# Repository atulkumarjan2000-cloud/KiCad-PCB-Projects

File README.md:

# KiCad-PCB-Projects
A collection of my KiCad Schematic, PCB design, Gerber and hardware projects

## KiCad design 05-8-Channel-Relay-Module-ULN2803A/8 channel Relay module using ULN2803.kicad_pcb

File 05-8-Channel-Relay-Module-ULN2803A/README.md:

# 8-Channel Relay Module Using ULN2803A

## Project Overview
This project focuses on designing an 8-channel relay module using KiCad EDA. The circuit uses a ULN2803A Darlington transistor array to drive eight relay channels from external control inputs.

## Features
- 8 independent relay output channels
- ULN2803A relay driver IC
- Input resistor network
- Individual LED indicators for relay channels
- Power input and status LED
- PCB design with mounting holes

## Design Tools
- KiCad EDA
- Schematic Design
- PCB Layout Design
- 3D PCB Visualization

## Project Files
- `8 Channel Relay Module using ULN2803.kicad_sch` — circuit schematic
- `8 Channel Relay Module using ULN2803.kicad_pcb` — PCB layout, when completed
- `8 Channel Relay Module using ULN2803.kicad_pro` — KiCad project configuration

## Applications
- Embedded systems
- Industrial control prototypes
- Home automation
- Microcontroller-based relay switching

## Safety Note
Verify relay coil voltage, contact ratings, driver connections, and PCB clearances before powering the circuit. Mains-voltage applications require appropriate isolation and safe enclosure design.

## Author
Atul

Designed using KiCad EDA.

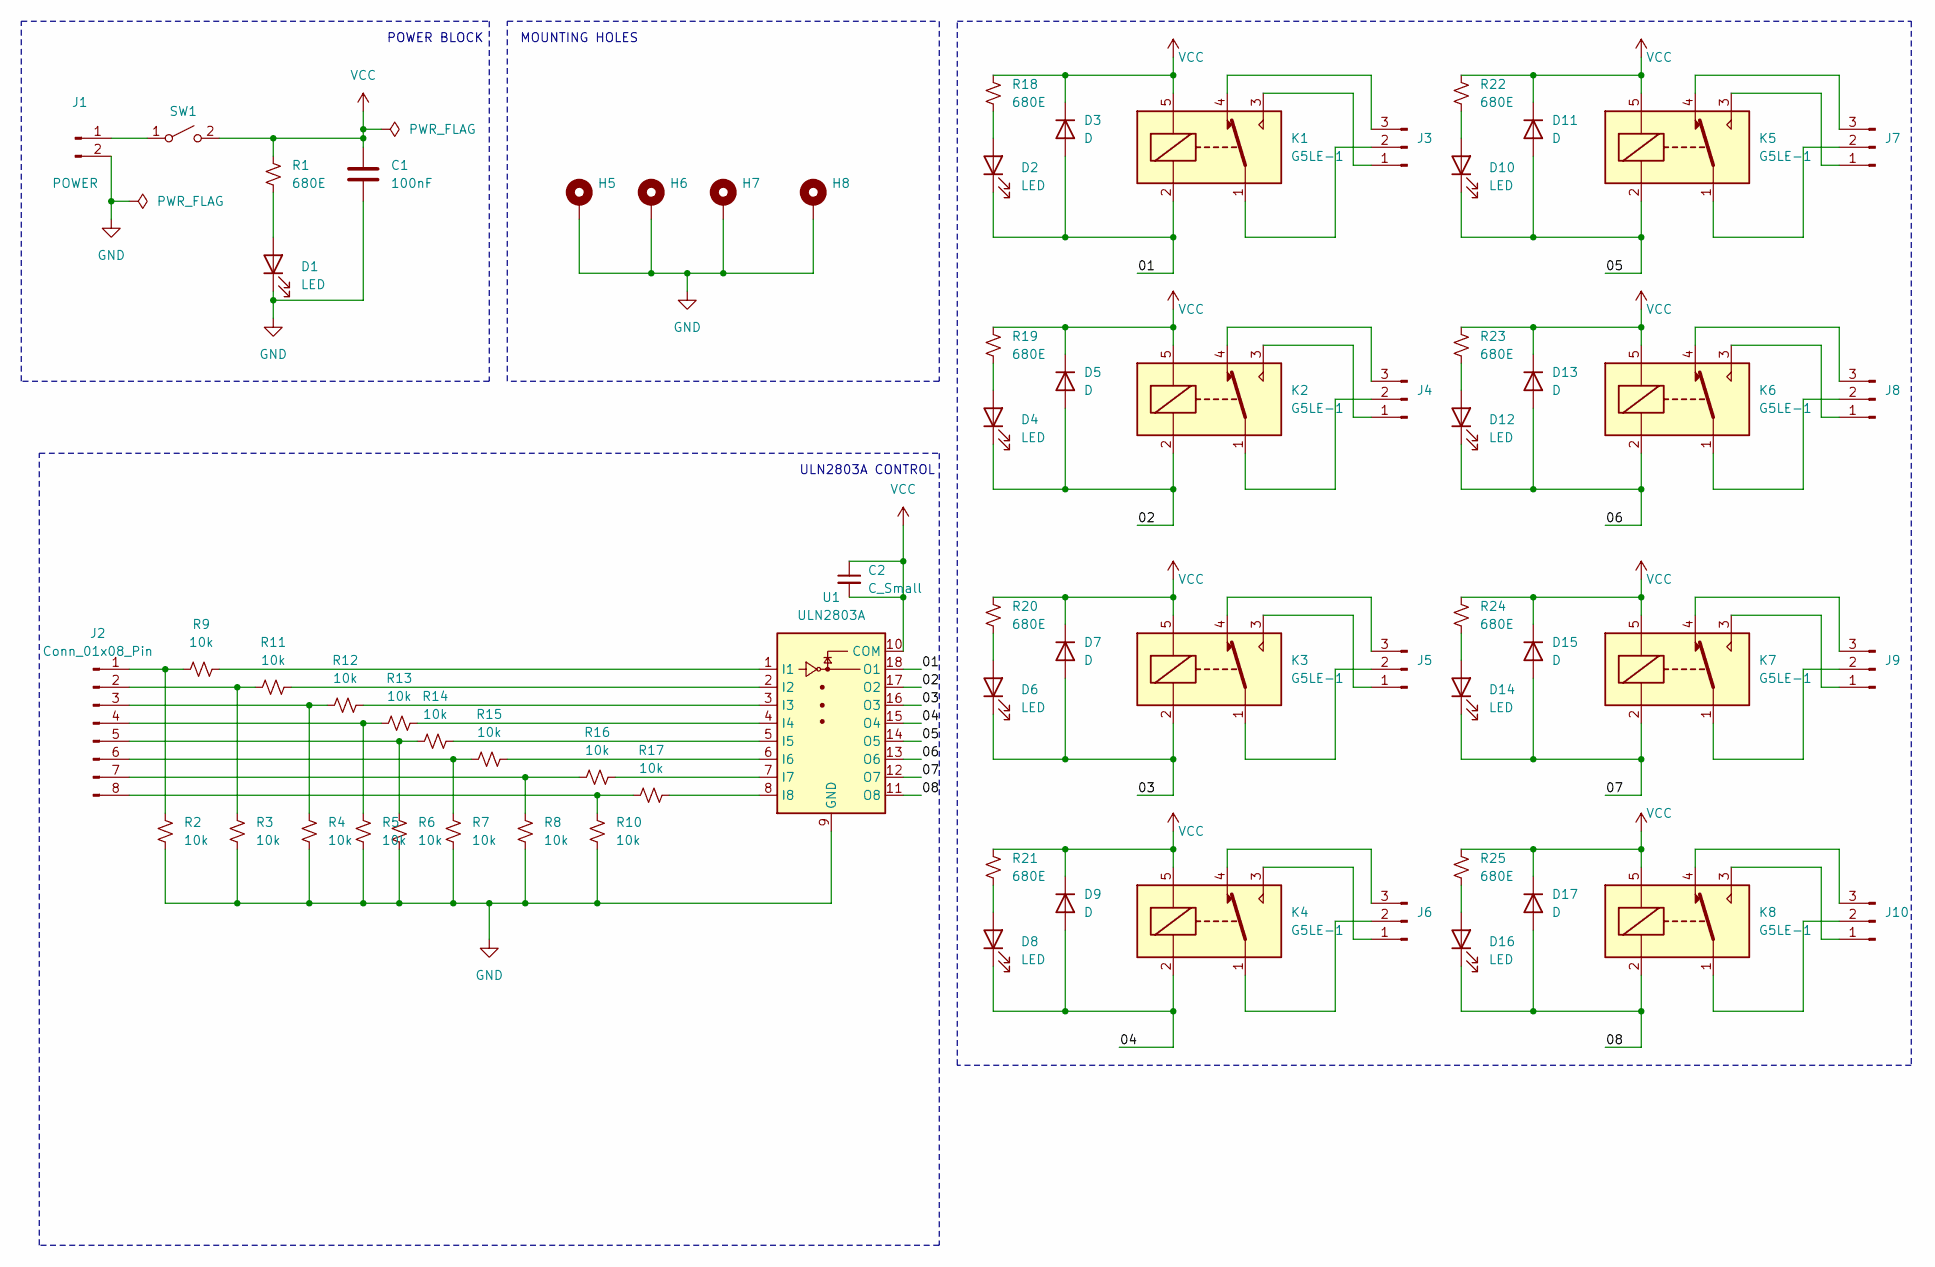
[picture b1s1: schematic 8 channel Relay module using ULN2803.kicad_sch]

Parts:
C1: 100nF; C_0805_2012Metric
C2: C_Small; C_0805_2012Metric
D1, D2, D4, D6, D8, D10, D12, D14, D16: LED; LED_1206_3216Metric
D3, D5, D7, D9, D11, D13, D15, D17: D; D_1206_3216Metric
H5, H6, H7, H8: MountingHole_Pad; MountingHole_2.5mm_Pad_Via
J1: POWER; JST_NV_B02P-NV_1x02_P5.00mm_Vertical
J2: Conn_01x08_Pin; PinHeader_1x08_P2.54mm_Vertical
J3, J4, J5, J6, J7, J8, J9, J10: Conn_01x03_Pin; JST_NV_B03P-NV_1x03_P5.00mm_Vertical
K1, K2, K3, K4, K5, K6, K7, K8: G5LE-1; Relay_SPDT_Omron-G5LE-1
R1, R18, R19, R20, R21, R22, R23, R24, R25: 680E; R_0805_2012Metric
R2, R3, R4, R5, R6, R7, R8, R9, R10, R11, R12, R13, R14, R15, R16, R17: 10k; R_0805_2012Metric
SW1: SW_DIP_SPSTx01_Slide_Copal_CHS-01A_W5.08mm_P1.27mm_JPin
U1: ULN2803A; DIP850W46P254L2324H393Q18

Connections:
/01: D2.1 (K), D3.2 (A), K1.2, U1.18 (O1)
/02: D4.1 (K), D5.2 (A), K2.2, U1.17 (O2)
/03: D6.1 (K), D7.2 (A), K3.2, U1.16 (O3)
/04: D8.1 (K), D9.2 (A), K4.2, U1.15 (O4)
/05: D10.1 (K), D11.2 (A), K5.2, U1.14 (O5)
/06: D12.1 (K), D13.2 (A), K6.2, U1.13 (O6)
/07: D14.1 (K), D15.2 (A), K7.2, U1.12 (O7)
/08: D16.1 (K), D17.2 (A), K8.2, U1.11 (O8)
GND: C1.2, D1.1 (K), H5.1 (1_1), H6.1 (1_1), H7.1 (1_1), H8.1 (1_1), J1.2, R2.2, R3.2, R4.2, R5.2, R6.2, R7.2, R8.2, R10.2, U1.9 (GND)
unnamed: D1.2 (A), R1.2
unnamed: D2.2 (A), R18.2
unnamed: D4.2 (A), R19.2
unnamed: D6.2 (A), R20.2
unnamed: D8.2 (A), R21.2
unnamed: D10.2 (A), R22.2
unnamed: D12.2 (A), R23.2
unnamed: D14.2 (A), R24.2
unnamed: D16.2 (A), R25.2
unnamed: J1.1, SW1.1 (A)
unnamed: J2.1, R2.1, R9.1
unnamed: J2.2, R3.1, R11.1
unnamed: J2.3, R4.1, R12.1
unnamed: J2.4, R5.1, R13.1
unnamed: J2.5, R6.1, R14.1
unnamed: J2.6, R7.1, R15.1
unnamed: J2.7, R8.1, R16.1
unnamed: J2.8, R10.1, R17.1
unnamed: J3.1, K1.3
unnamed: J3.2, K1.1
unnamed: J3.3, K1.4
unnamed: J4.1, K2.3
unnamed: J4.2, K2.1
unnamed: J4.3, K2.4
unnamed: J5.1, K3.3
unnamed: J5.2, K3.1
unnamed: J5.3, K3.4
unnamed: J6.1, K4.3
unnamed: J6.2, K4.1
unnamed: J6.3, K4.4
unnamed: J7.1, K5.3
unnamed: J7.2, K5.1
unnamed: J7.3, K5.4
unnamed: J8.1, K6.3
unnamed: J8.2, K6.1
unnamed: J8.3, K6.4
unnamed: J9.1, K7.3
unnamed: J9.2, K7.1
unnamed: J9.3, K7.4
unnamed: J10.1, K8.3
unnamed: J10.2, K8.1
unnamed: J10.3, K8.4
unnamed: R9.2, U1.1 (I1)
unnamed: R11.2, U1.2 (I2)
unnamed: R12.2, U1.3 (I3)
unnamed: R13.2, U1.4 (I4)
unnamed: R14.2, U1.5 (I5)
unnamed: R15.2, U1.6 (I6)
unnamed: R16.2, U1.7 (I7)
unnamed: R17.2, U1.8 (I8)
VCC: C1.1, C2.1, C2.2, D3.1 (K), D5.1 (K), D7.1 (K), D9.1 (K), D11.1 (K), D13.1 (K), D15.1 (K), D17.1 (K), K1.5, K2.5, K3.5, K4.5, K5.5, K6.5, K7.5, K8.5, R1.1, R18.1, R19.1, R20.1, R21.1, R22.1, R23.1, R24.1, R25.1, SW1.2 (B), U1.10 (COM)

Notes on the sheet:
MOUNTING HOLES
ULN2803A CONTROL
POWER BLOCK

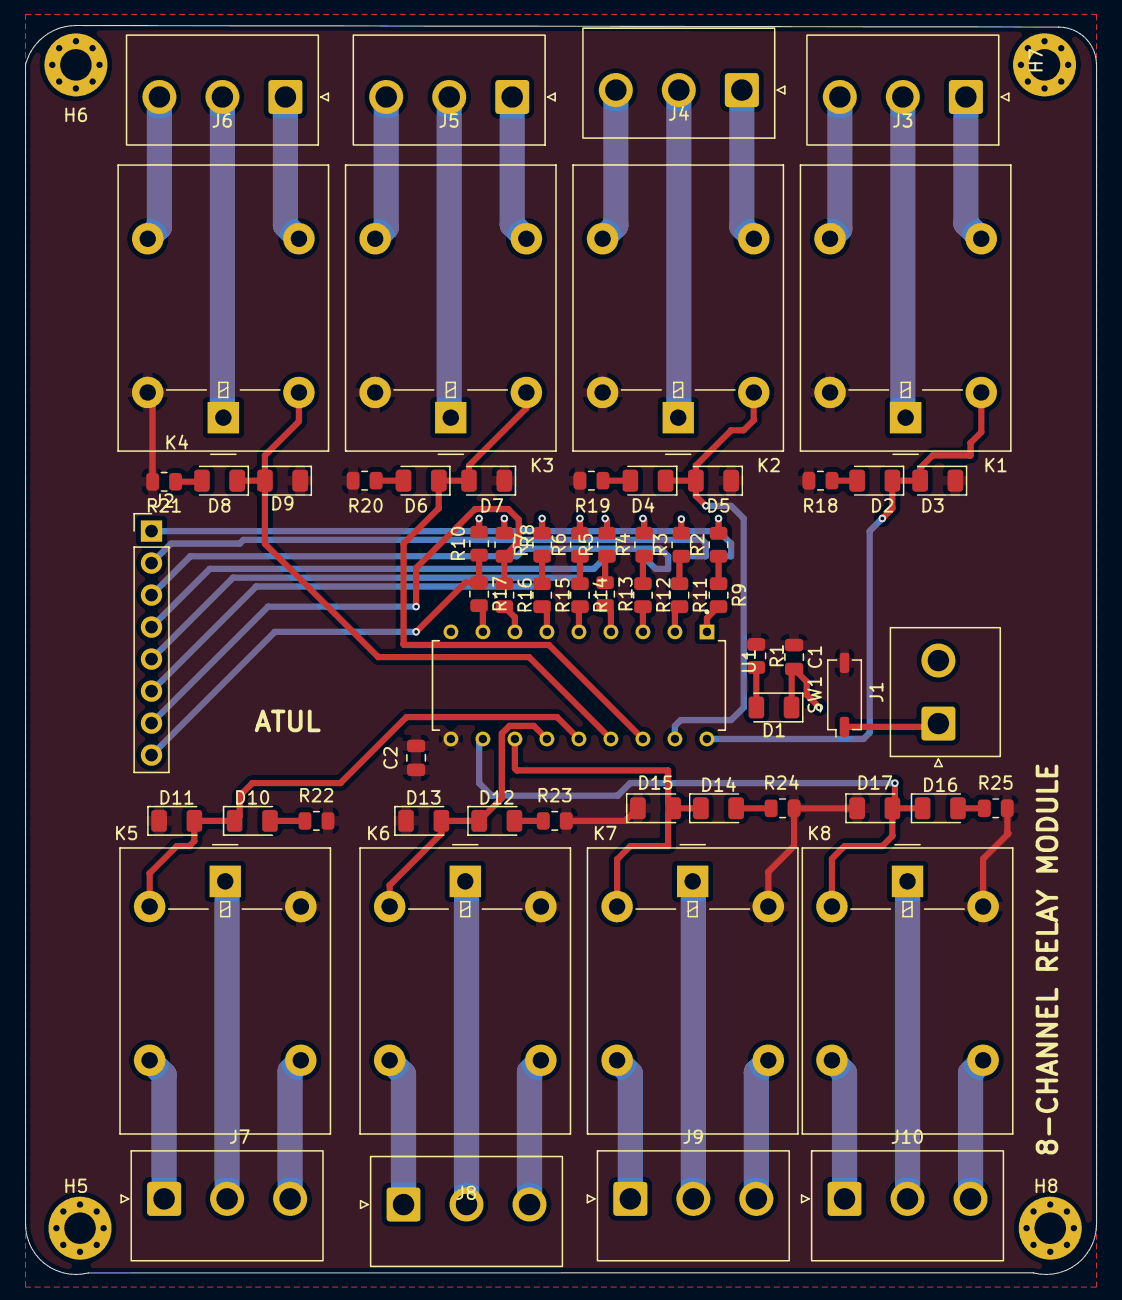
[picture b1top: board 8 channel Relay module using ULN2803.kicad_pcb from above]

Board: 2 copper layers, 85.0 x 99.1 mm, 68 parts (0 on the bottom side), 60 nets.

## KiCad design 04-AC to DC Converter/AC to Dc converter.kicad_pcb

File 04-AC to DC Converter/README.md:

# 12V AC to DC Converter

A custom 12V AC to DC  Converter/rectifier and filtered power supply PCB designed using KiCad.

## Project Overview

This project converts 12V AC input into filtered DC output using a full-wave bridge rectifier and smoothing capacitor.

## Main Components

- D1–D4: Bridge Rectifier
- C1: Smoothing Capacitor
- D5: Power Indicator LED
- R1/R2: Resistors
- J1: 12V AC Input
- J2: DC Output

## Tools Used

- KiCad
- Schematic Design
- PCB Design

## PCB Views

### 3D View

### PCB Layout

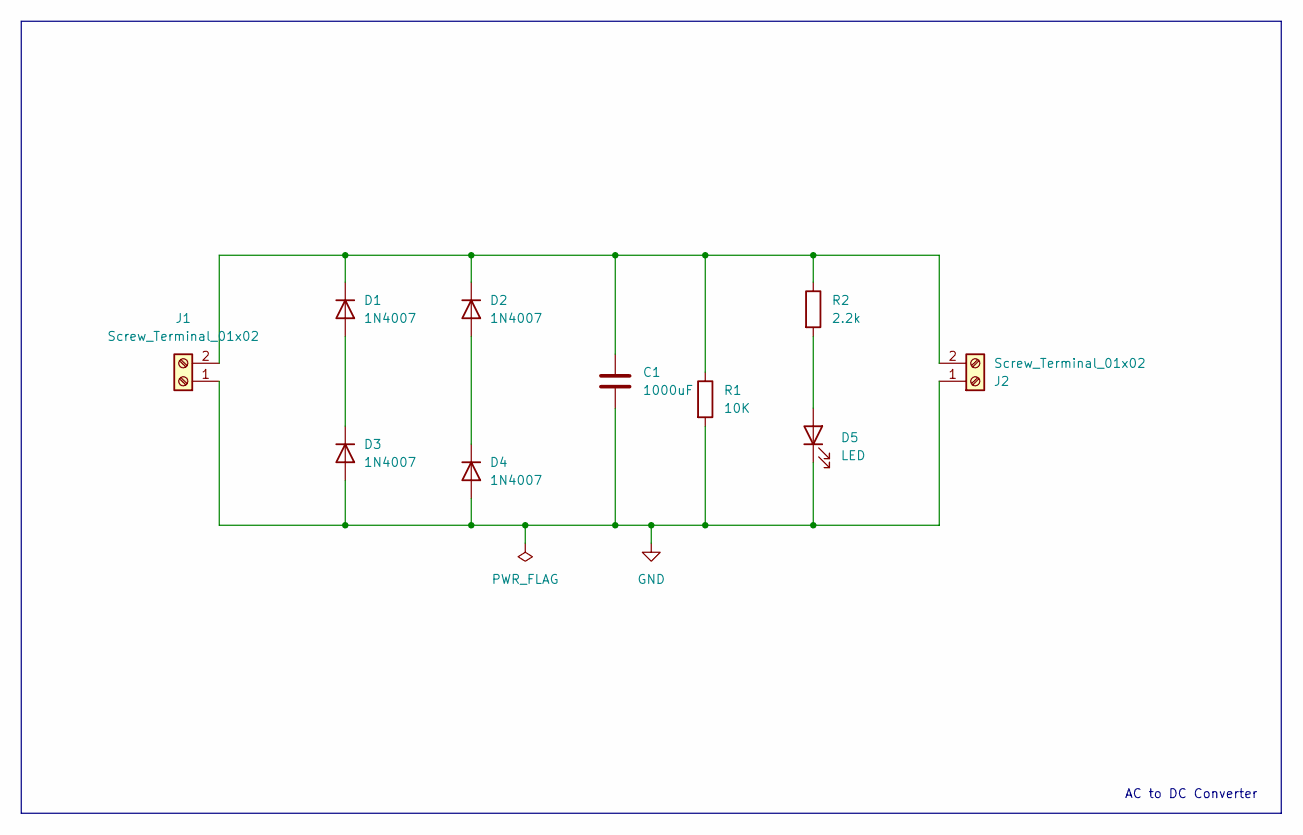
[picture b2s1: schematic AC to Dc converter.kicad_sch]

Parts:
C1: 1000uF; C_Radial_D8.0mm_H11.5mm_P3.50mm
D1, D2, D3, D4: 1N4007; D_DO-41_SOD81_P10.16mm_Horizontal
D5: LED; LED_D5.0mm
J1, J2: Screw_Terminal_01x02; TerminalBlock_MaiXu_MX126-5.0-02P_1x02_P5.00mm
R1: 10K; R_Axial_DIN0207_L6.3mm_D2.5mm_P7.62mm_Horizontal
R2: 2.2k; R_Axial_DIN0207_L6.3mm_D2.5mm_P7.62mm_Horizontal

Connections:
GND: C1.2, D3.2 (A), D4.2 (A), D5.1 (K), J1.1, J2.1, R1.2
unnamed: D1.2 (A), D3.1 (K)
unnamed: C1.1, D1.1 (K), D2.1 (K), J1.2, J2.2, R1.1, R2.1
unnamed: D2.2 (A), D4.1 (K)
unnamed: D5.2 (A), R2.2

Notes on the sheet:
AC to DC Converter

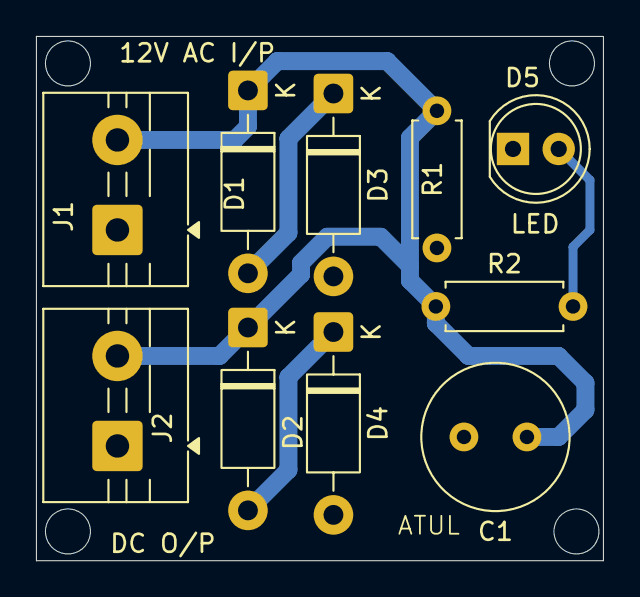
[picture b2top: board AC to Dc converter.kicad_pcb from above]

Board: 2 copper layers, 31.5 x 29.1 mm, 10 parts (0 on the bottom side), 5 nets.

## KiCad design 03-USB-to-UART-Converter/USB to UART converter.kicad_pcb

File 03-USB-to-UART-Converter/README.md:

# USB to UART Converter C-Type

A custom USB to UART Converter PCB designed using KiCad.

## Project Overview

This project contains the complete schematic and PCB design of a USB to UART Converter with a Type-C interface.

## Tools Used

- KiCad
- Schematic Design
- PCB Design

## Project Files

- KiCad Schematic
- KiCad PCB Layout
- KiCad Project File

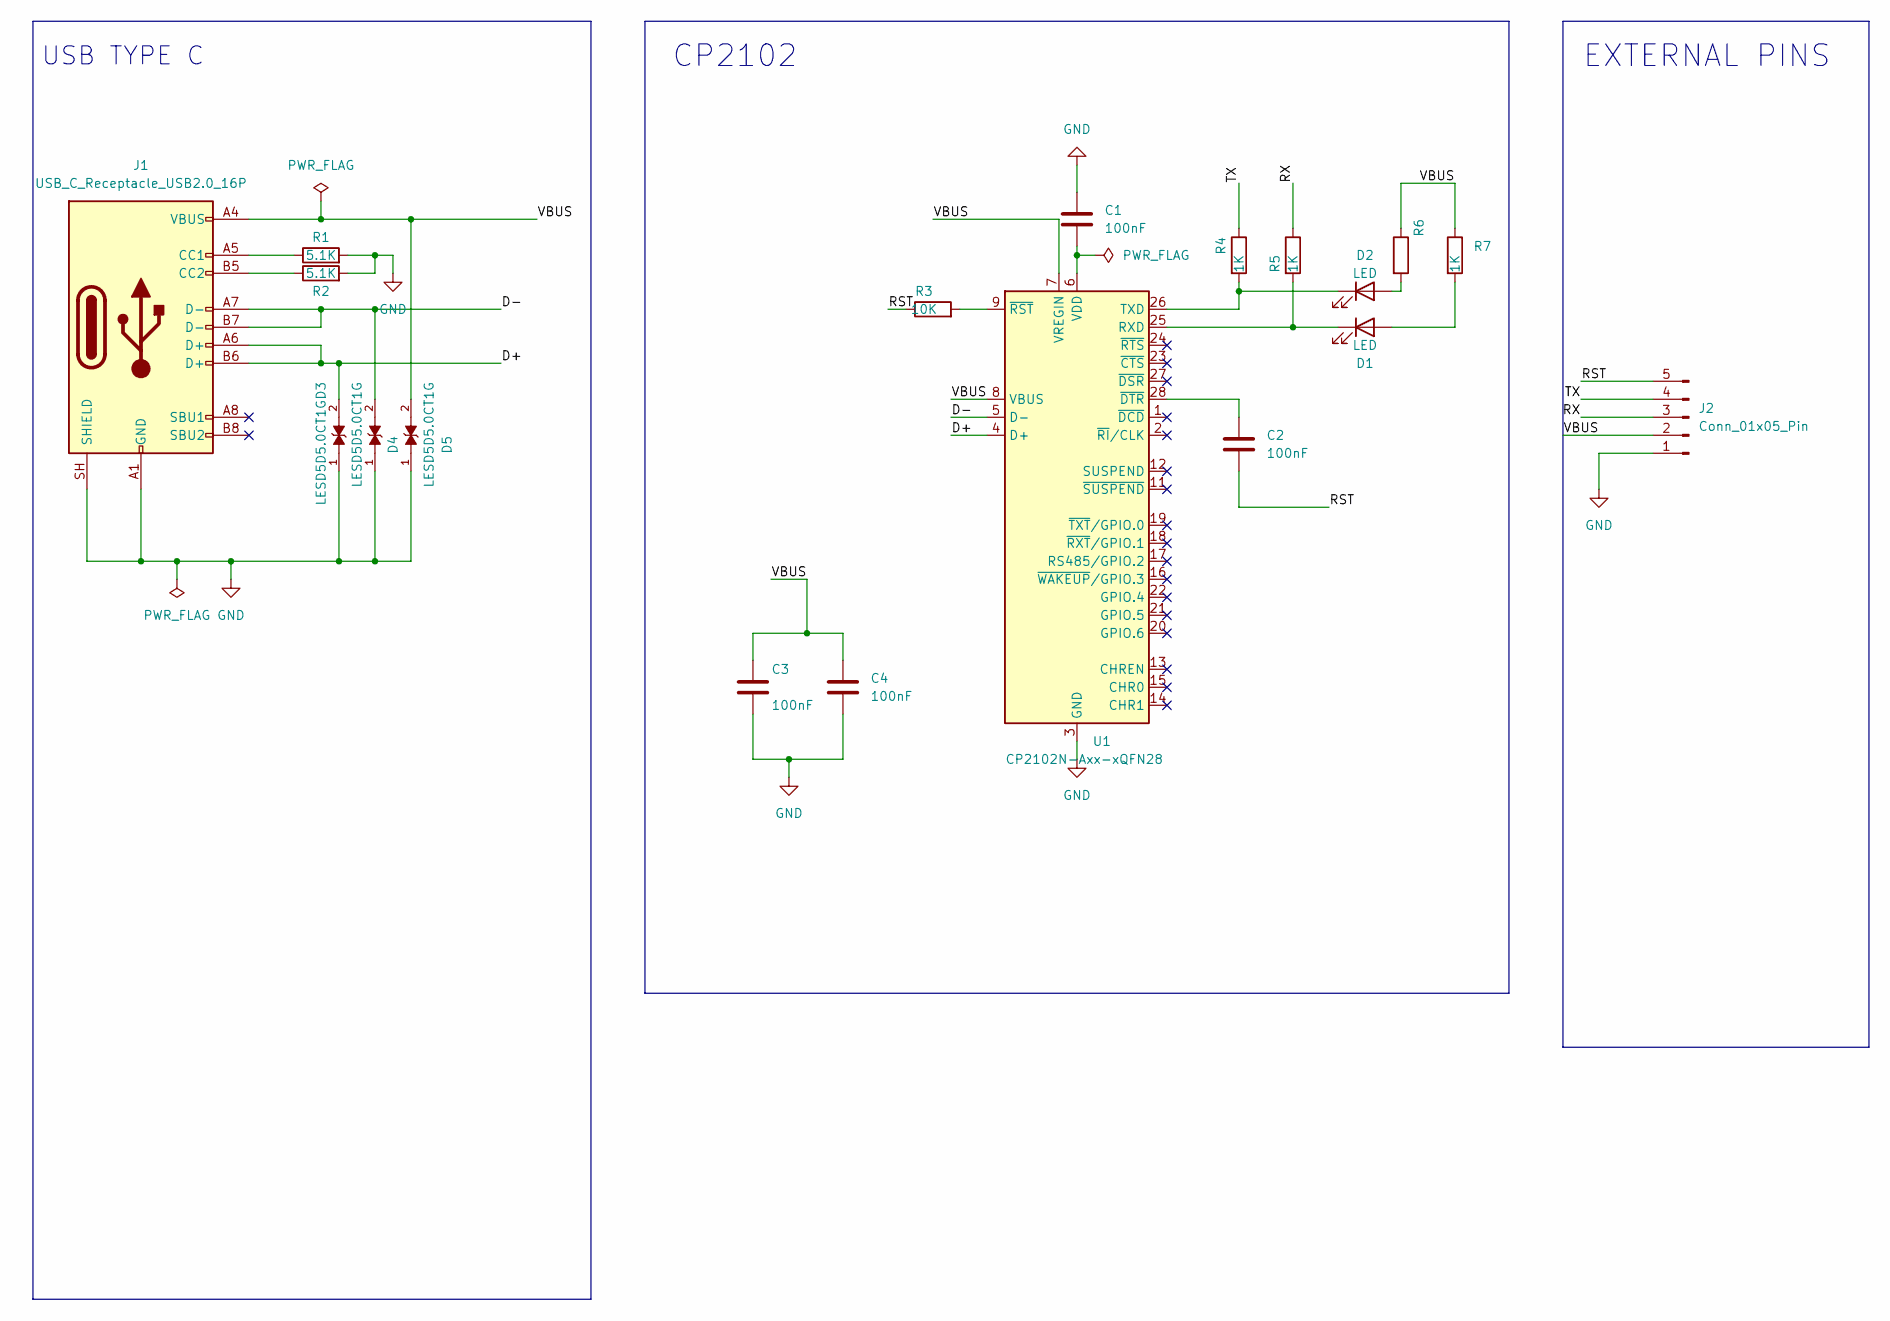
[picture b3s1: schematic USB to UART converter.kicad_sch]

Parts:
C1, C2, C3, C4: 100nF; C_0201_0603Metric
D1, D2: LED; LED_0201_0603Metric
D3, D4, D5: LESD5D5.0CT1G; TVS_LESD5D5.0CT1G; PARTREV O
J1: USB_C_Receptacle_USB2.0_16P; USB_C_Receptacle_HRO_TYPE-C-31-M-12
J2: Conn_01x05_Pin; PinHeader_1x05_P2.54mm_Horizontal
R1, R2: 5.1K; R_0201_0603Metric
R3: 10K; R_0201_0603Metric
R4, R5, R6, R7: 1K; R_0201_0603Metric
U1: CP2102N-Axx-xQFN28; QFN-28-1EP_5x5mm_P0.5mm_EP3.35x3.35mm

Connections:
/D+: D3.2, J1.A6 (D+), J1.B6 (D+), U1.4 (D+)
/D-: D4.2, J1.A7 (D-), J1.B7 (D-), U1.5 (D-)
/RST: C2.1, J2.5, R3.1
/RX: J2.3, R5.1
/TX: J2.4, R4.1
/VBUS: C3.1, C4.1, D5.2, J1.A4 (VBUS), J1.A9 (VBUS), J1.B4 (VBUS), J1.B9 (VBUS), J2.2, R6.1, R7.1, U1.7 (VREGIN), U1.8 (VBUS)
GND: C1.1, C3.2, C4.2, D3.1, D4.1, D5.1, J1.A1 (GND), J1.A12 (GND), J1.B1 (GND), J1.B12 (GND), J1.SH (SHIELD), J2.1, R1.2, R2.2, U1.3 (GND), U1.29 (GND)
unnamed: D1.2 (A), R7.2
unnamed: D1.1 (K), R5.2, U1.25 (RXD)
unnamed: D2.2 (A), R6.2
unnamed: D2.1 (K), R4.2, U1.26 (TXD)
unnamed: J1.A5 (CC1), R1.1
unnamed: J1.B5 (CC2), R2.1
unnamed: C1.2, U1.6 (VDD)
unnamed: C2.2, U1.28 (~DTR)
unnamed: R3.2, U1.9 (~RST)

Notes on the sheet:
CP2102
EXTERNAL PINS
USB TYPE C

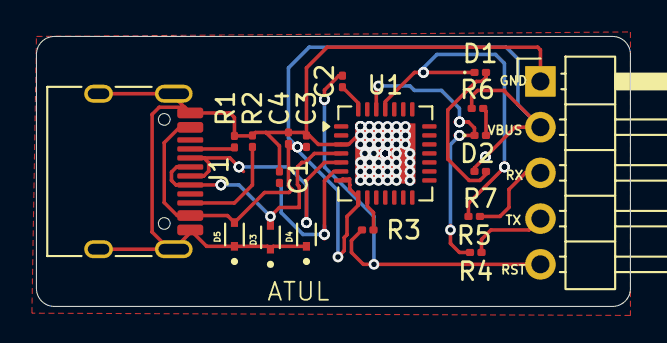
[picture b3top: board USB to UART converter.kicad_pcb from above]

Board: 2 copper layers, 33.0 x 15.0 mm, 19 parts (0 on the bottom side), 16 nets.

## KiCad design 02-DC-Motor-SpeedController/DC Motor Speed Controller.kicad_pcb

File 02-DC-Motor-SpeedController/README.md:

# DC Motor Speed Controller

A custom DC Motor Speed Controller PCB designed using KiCad.

## Project Overview

This project contains the schematic and PCB design for controlling the speed of a DC motor.

## Tools Used

- KiCad
- Schematic Design
- PCB Design

## Project Files

- KiCad Schematic
- PCB Layout
- 3D PCB View

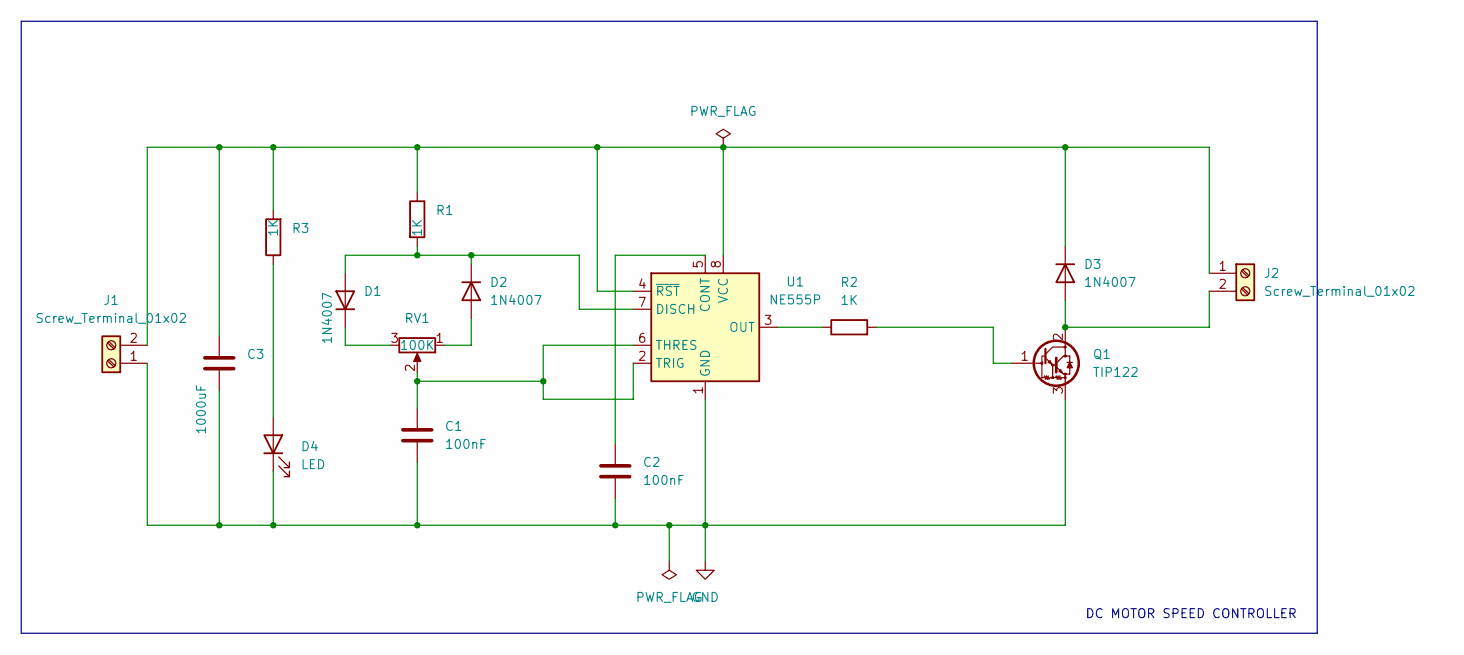
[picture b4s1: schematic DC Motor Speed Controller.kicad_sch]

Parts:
C1, C2: 100nF; C_Disc_D4.7mm_W2.5mm_P5.00mm
C3: 1000uF; CP_Radial_D10.0mm_P5.00mm
D1, D2, D3: 1N4007; D_DO-41_SOD81_P10.16mm_Horizontal
D4: LED; LED_D5.0mm
J1, J2: Screw_Terminal_01x02; TerminalBlock_Xinya_XY308-2.54-2P_1x02_P2.54mm_Horizontal
Q1: TIP122; TO-220-3_Vertical
R1, R2, R3: 1K; R_Axial_DIN0204_L3.6mm_D1.6mm_P7.62mm_Horizontal
RV1: 100K; Potentiometer_Alps_RK163_Single_Horizontal
U1: NE555P; DIP-8_W7.62mm

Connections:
GND: C1.2, C2.2, C3.2, D4.1 (K), J1.1, Q1.3 (E), U1.1 (GND)
unnamed: D1.2 (A), D2.1 (K), R1.2, U1.7 (DISCH)
unnamed: D1.1 (K), RV1.3
unnamed: D2.2 (A), RV1.1
unnamed: D3.2 (A), J2.2, Q1.2 (C)
unnamed: C3.1, D3.1 (K), J1.2, J2.1, R1.1, R3.2, U1.4 (~RST), U1.8 (VCC)
unnamed: D4.2 (A), R3.1
unnamed: Q1.1 (B), R2.2
unnamed: C2.1, U1.5 (CONT)
unnamed: R2.1, U1.3 (OUT)
unnamed: C1.1, RV1.2, U1.2 (TRIG), U1.6 (THRES)

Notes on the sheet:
DC MOTOR SPEED CONTROLLER

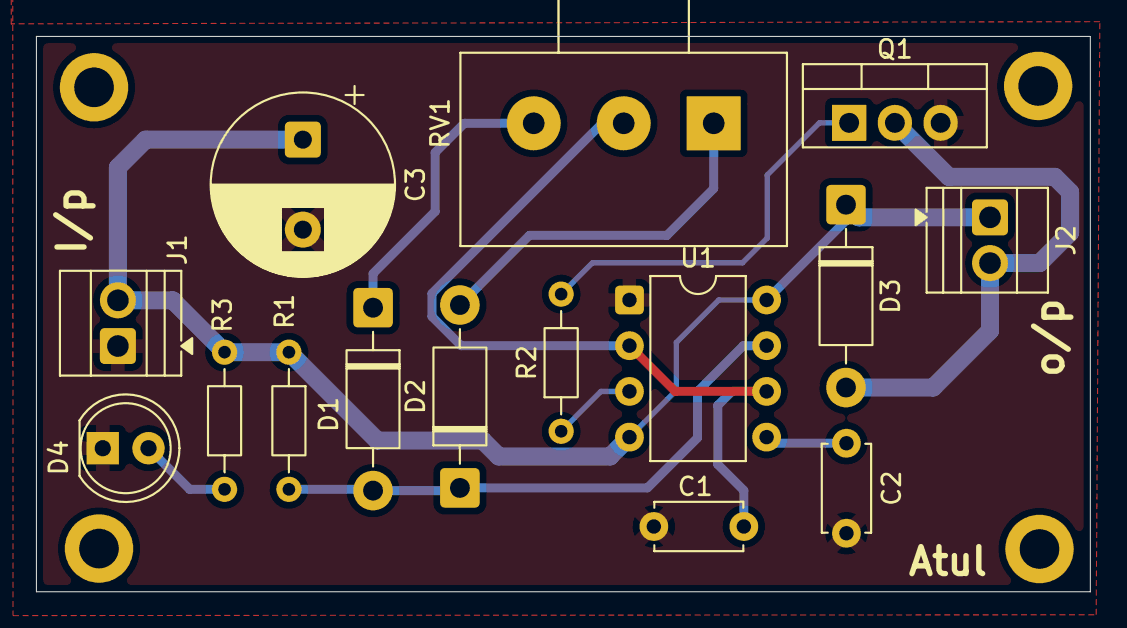
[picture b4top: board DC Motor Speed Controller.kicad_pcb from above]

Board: 2 copper layers, 58.5 x 30.8 mm, 15 parts (0 on the bottom side), 11 nets.

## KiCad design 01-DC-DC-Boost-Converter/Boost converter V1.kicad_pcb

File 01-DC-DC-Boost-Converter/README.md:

# DC-DC Boost Converter

A custom DC-DC Boost Converter PCB designed using KiCad.

## Project Overview

This project contains the complete schematic and PCB design of a DC-DC Boost Converter.

## Tools Used

- KiCad
- PCB Design
- Schematic Design

## Project Files

- KiCad Schematic
- PCB Layout
- Gerber Files
- 3D PCB Model

## PCB Preview

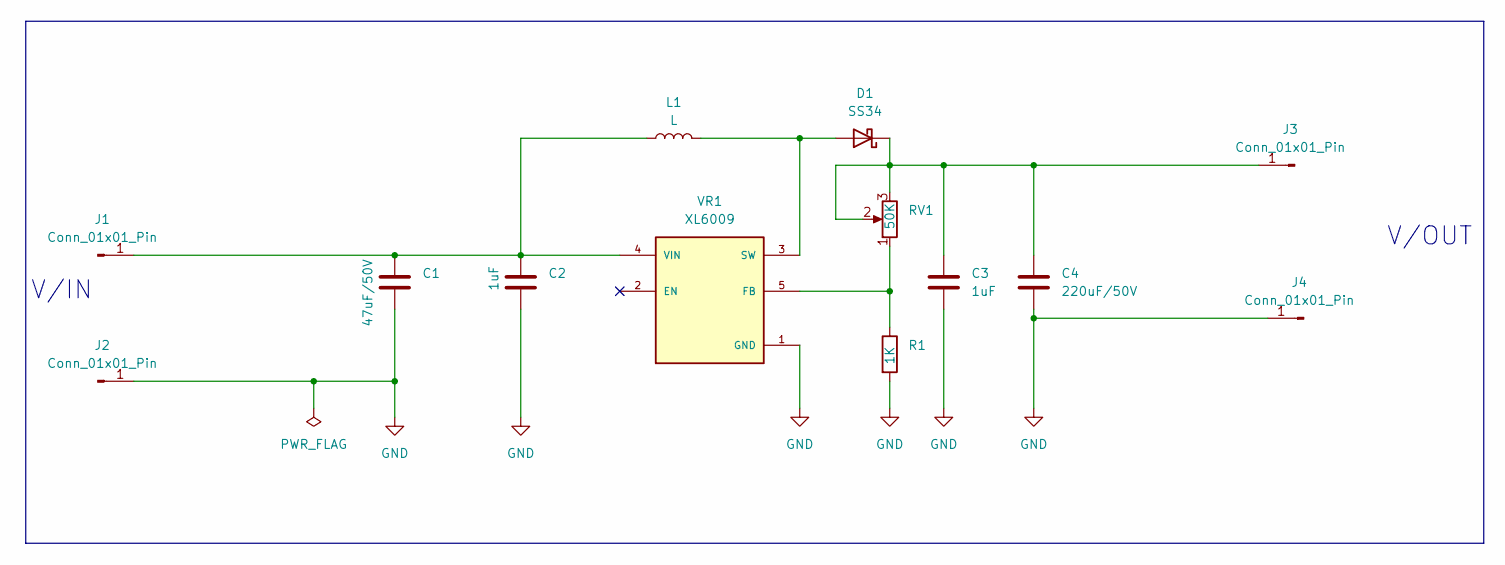
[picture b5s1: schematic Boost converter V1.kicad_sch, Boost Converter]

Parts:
C1: 47uF/50V; CP_Radial_D8.0mm_P3.50mm
C2, C3: 1uF; C_0805_2012Metric
C4: 220uF/50V; CP_Radial_D8.0mm_P3.50mm
D1: SS34; D_SMA
J1, J2, J3, J4: Conn_01x01_Pin; PinHeader_1x01_P2.54mm_Horizontal
L1: L; L_12x12mm_H8mm
R1: 1K; R_1206_3216Metric
RV1: 50K; Potentiometer_Bourns_3299W_Vertical
VR1: XL6009; DPAK170P1435X465-6N; PARTREV 1.1

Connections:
GND: C1.2, C2.2, C3.2, C4.2, J2.1 (Pin_1_1), J4.1 (Pin_1_1), R1.2, VR1.1 (GND)
unnamed: D1.2 (A), L1.2, VR1.3 (SW), VR1.6 (SW)
unnamed: C3.1, C4.1, D1.1 (K), J3.1 (Pin_1_1), RV1.2, RV1.3
unnamed: C1.1, C2.1, J1.1 (Pin_1_1), L1.1, VR1.4 (VIN)
unnamed: R1.1, RV1.1, VR1.5 (FB)

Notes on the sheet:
V/IN
V/OUT

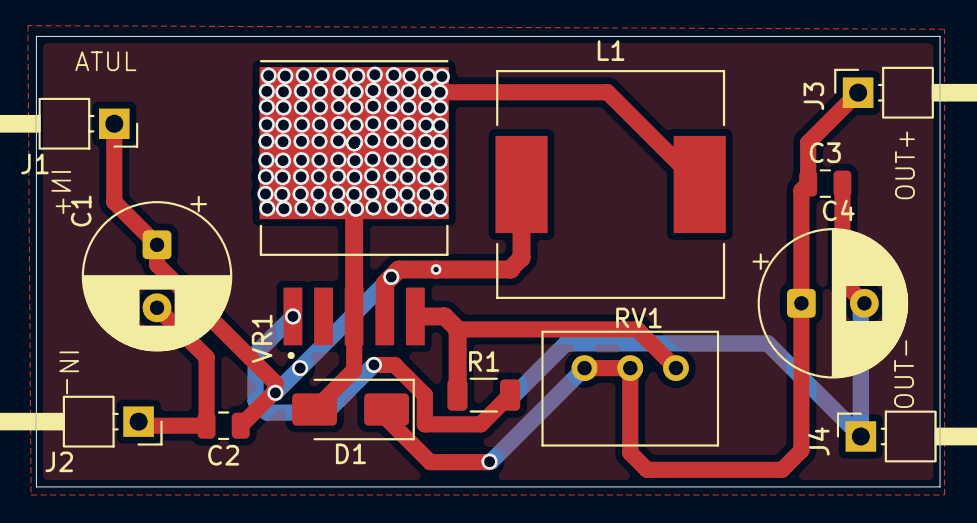
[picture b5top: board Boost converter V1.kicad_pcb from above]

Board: 2 copper layers, 50.2 x 25.0 mm, 13 parts (0 on the bottom side), 5 nets.
